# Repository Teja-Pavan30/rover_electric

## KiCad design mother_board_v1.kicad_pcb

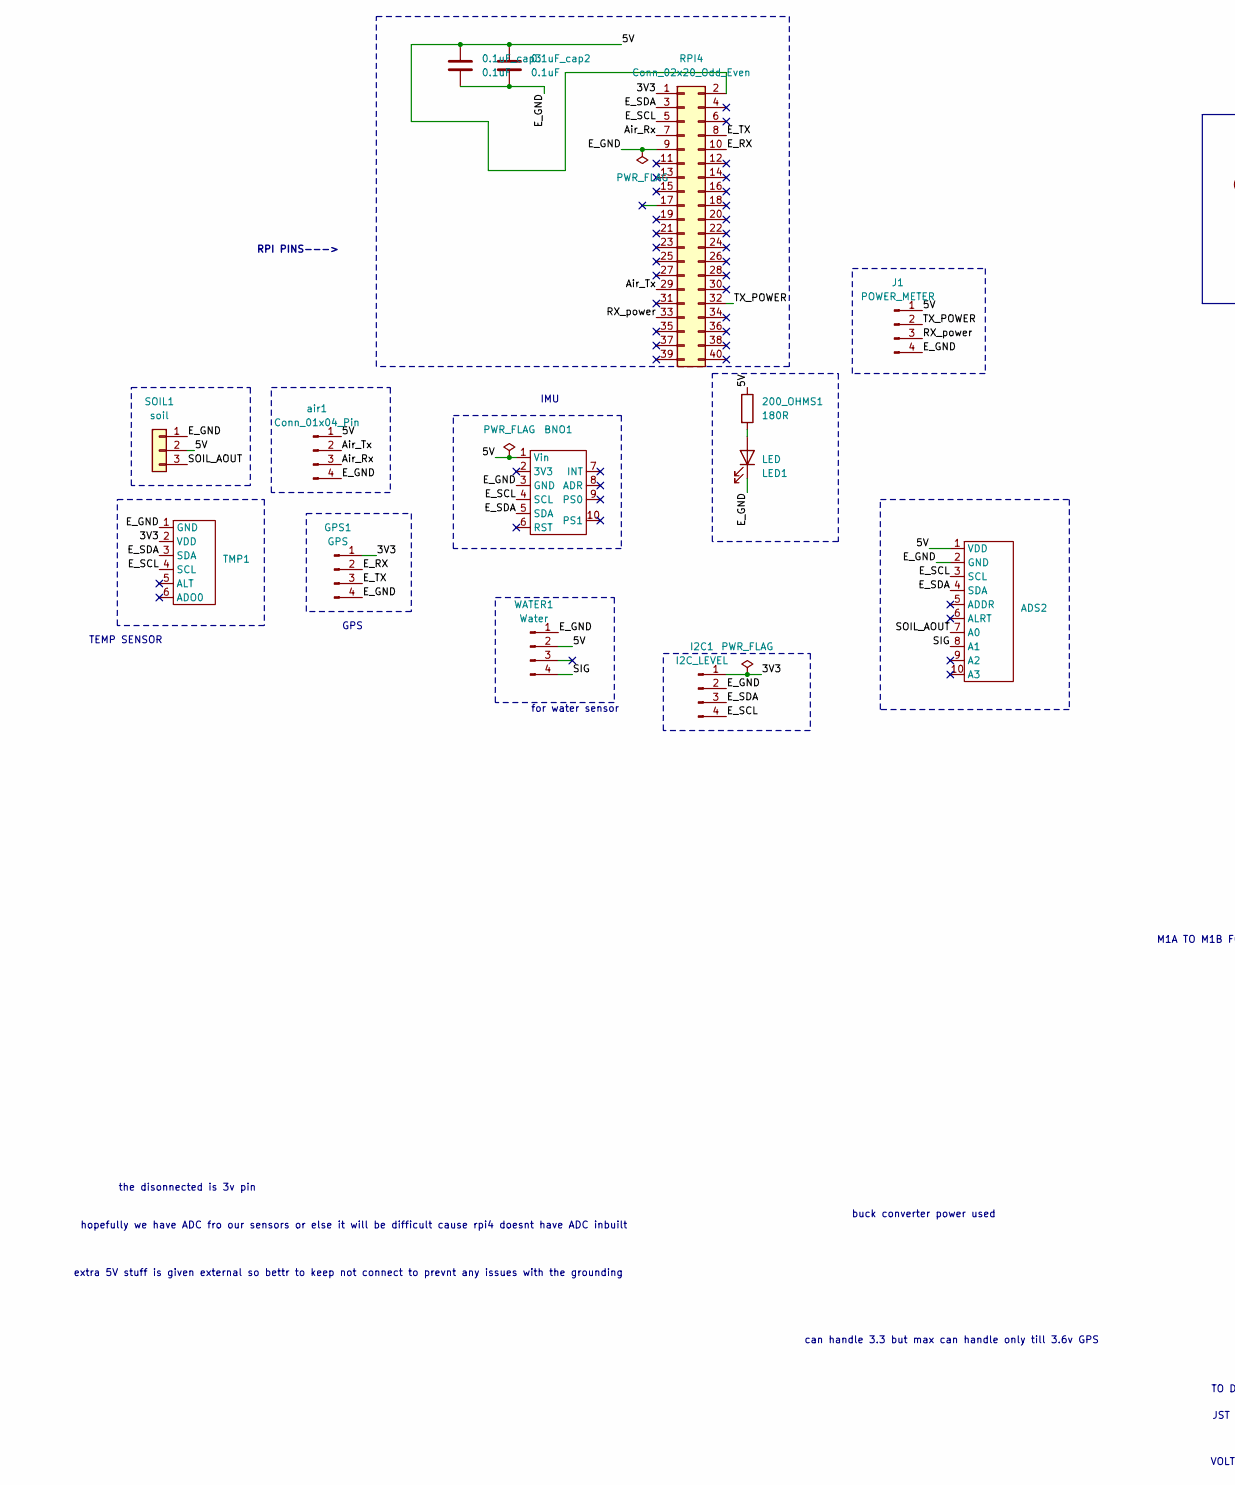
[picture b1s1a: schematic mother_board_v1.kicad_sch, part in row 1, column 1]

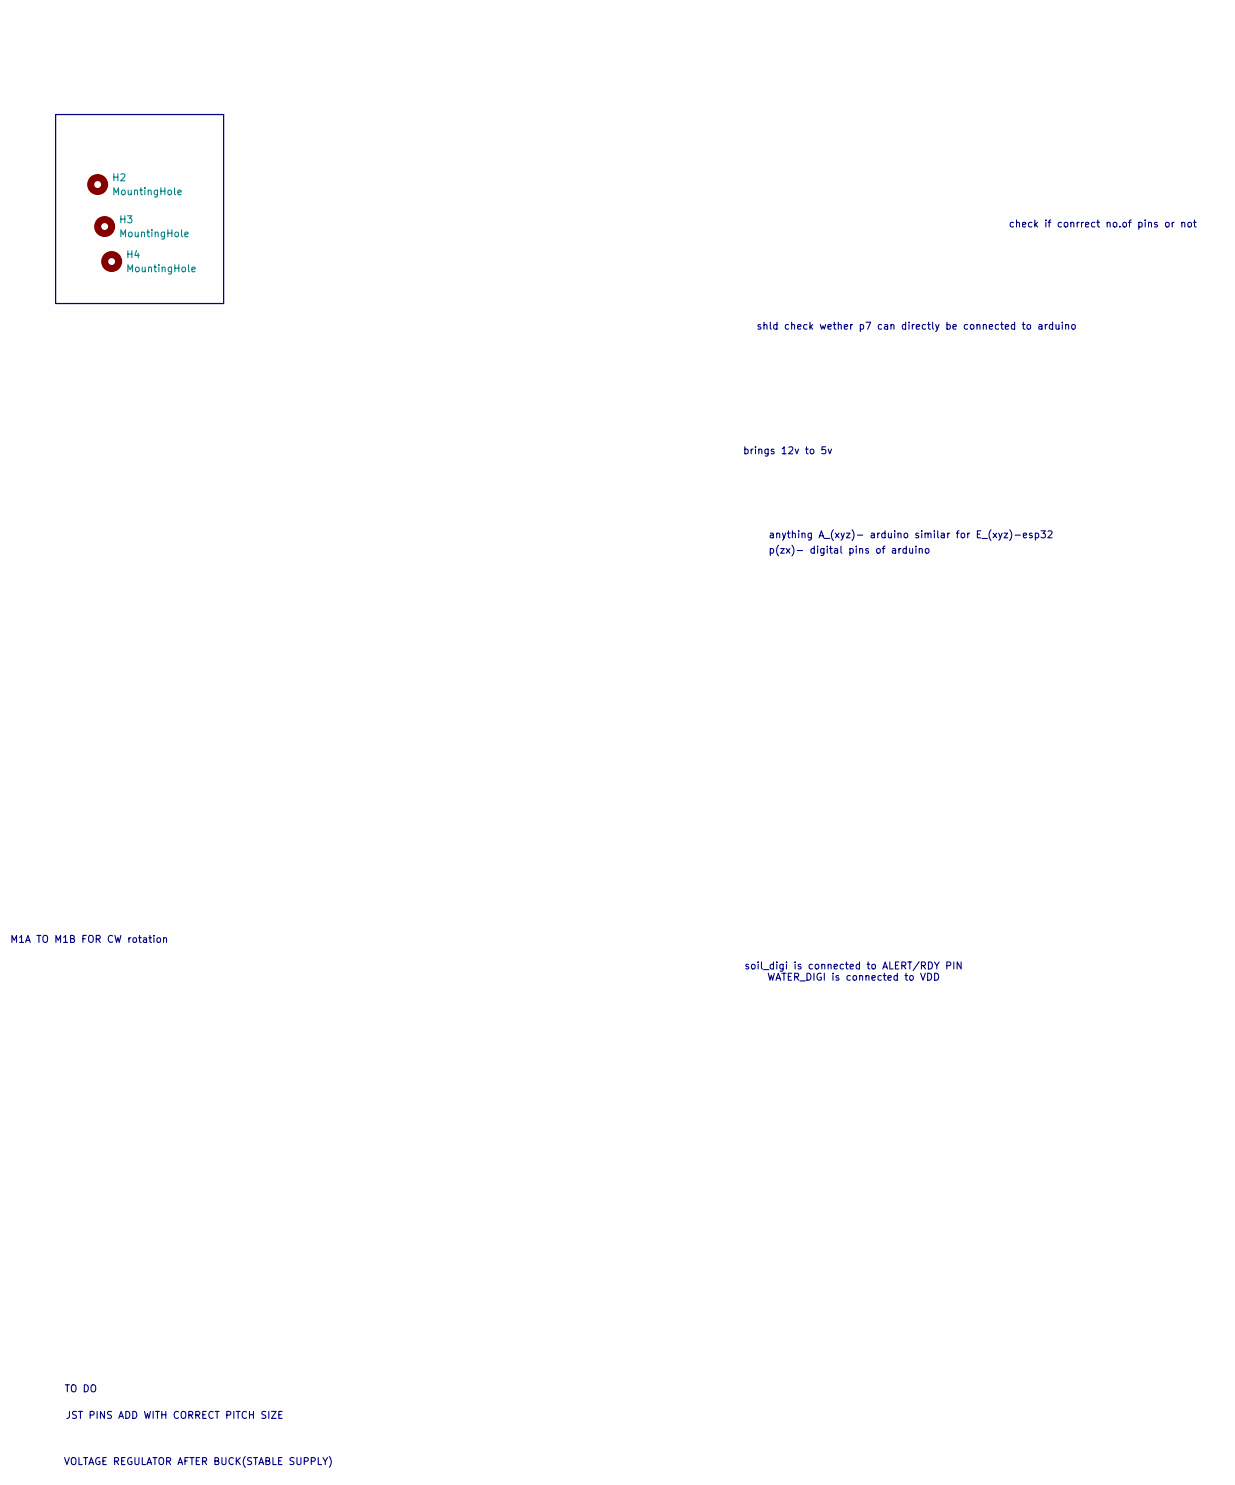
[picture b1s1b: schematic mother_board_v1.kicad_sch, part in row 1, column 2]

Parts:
0.1uF_cap2, 0.1uF_cap3: 0.1uF; C_Disc_D3.0mm_W1.6mm_P2.50mm
200_OHMS1: 180R; R_Axial_DIN0414_L11.9mm_D4.5mm_P15.24mm_Horizontal
ADS2: ADS1115
BNO1: ADAFRUIT-BNO055-STEMMA-QT
GPS1: GPS; JST_XH_B4B-XH-AM_1x04_P2.50mm_Vertical
H2, H3, H4: MountingHole; MountingHole_3.2mm_M3_ISO7380_Pad
I2C1: I2C_LEVEL; JST_XH_B4B-XH-AM_1x04_P2.50mm_Vertical
J1: POWER_METER; JST_XH_B4B-XH-AM_1x04_P2.50mm_Vertical
LED1: LED; LED_D5.0mm
RPI4: Conn_02x20_Odd_Even; IDC-Header_2x20_P2.54mm_Vertical
SOIL1: soil; JST_XH_B3B-XH-A_1x03_P2.50mm_Vertical
TMP1: TMP102
WATER1: Water; JST_XH_B4B-XH-AM_1x04_P2.50mm_Vertical
air1: Conn_01x04_Pin; JST_XH_B4B-XH-AM_1x04_P2.50mm_Vertical

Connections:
/3V3: GPS1.1, I2C1.1, RPI4.1, TMP1.2 (VDD)
/5V: 0.1uF_cap2.2, 0.1uF_cap3.2, 200_OHMS1.1, ADS2.1 (VDD), BNO1.1 (Vin), J1.1, RPI4.2, SOIL1.2, WATER1.2, air1.1
/Air_Rx: RPI4.7, air1.3
/Air_Tx: RPI4.29, air1.2
/E_GND: 0.1uF_cap2.1, 0.1uF_cap3.1, ADS2.2 (GND), BNO1.3 (GND), GPS1.4, I2C1.2, J1.4, LED1.1 (K), RPI4.9, SOIL1.1, TMP1.1 (GND), WATER1.1, air1.4
/E_RX: GPS1.2, RPI4.10
/E_SCL: ADS2.3 (SCL), BNO1.4 (SCL), I2C1.4, RPI4.5, TMP1.4 (SCL)
/E_SDA: ADS2.4 (SDA), BNO1.5 (SDA), I2C1.3, RPI4.3, TMP1.3 (SDA)
/E_TX: GPS1.3, RPI4.8
/RX_power: J1.3, RPI4.33
/SIG: ADS2.8 (A1), WATER1.4
/SOIL_AOUT: ADS2.7 (A0), SOIL1.3
/TX_POWER: J1.2, RPI4.32
unnamed: 200_OHMS1.2, LED1.2 (A)

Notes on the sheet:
anything A_(xyz)- arduino similar for E_(xyz)-esp32
VOLTAGE REGULATOR AFTER BUCK(STABLE SUPPLY)
buck converter power used
extra 5V stuff is given external so bettr to keep not connect to prevnt any issues with the grounding
TEMP SENSOR
M1A TO M1B FOR CW rotation
IMU
for water sensor
brings 12v to 5v
GPS
TO DO
the disonnected is 3v pin
can handle 3.3 but max can handle only till 3.6v GPS
shld check wether p7 can directly be connected to arduino
hopefully we have ADC fro our sensors or else it will be difficult cause rpi4 doesnt have ADC inbuilt
p(zx)- digital pins of arduino
check if conrrect no.of pins or not
soil_digi is connected to ALERT/RDY PIN WATER_DIGI is connected to VDD
RPI PINS--->
JST PINS ADD WITH CORRECT PITCH SIZE

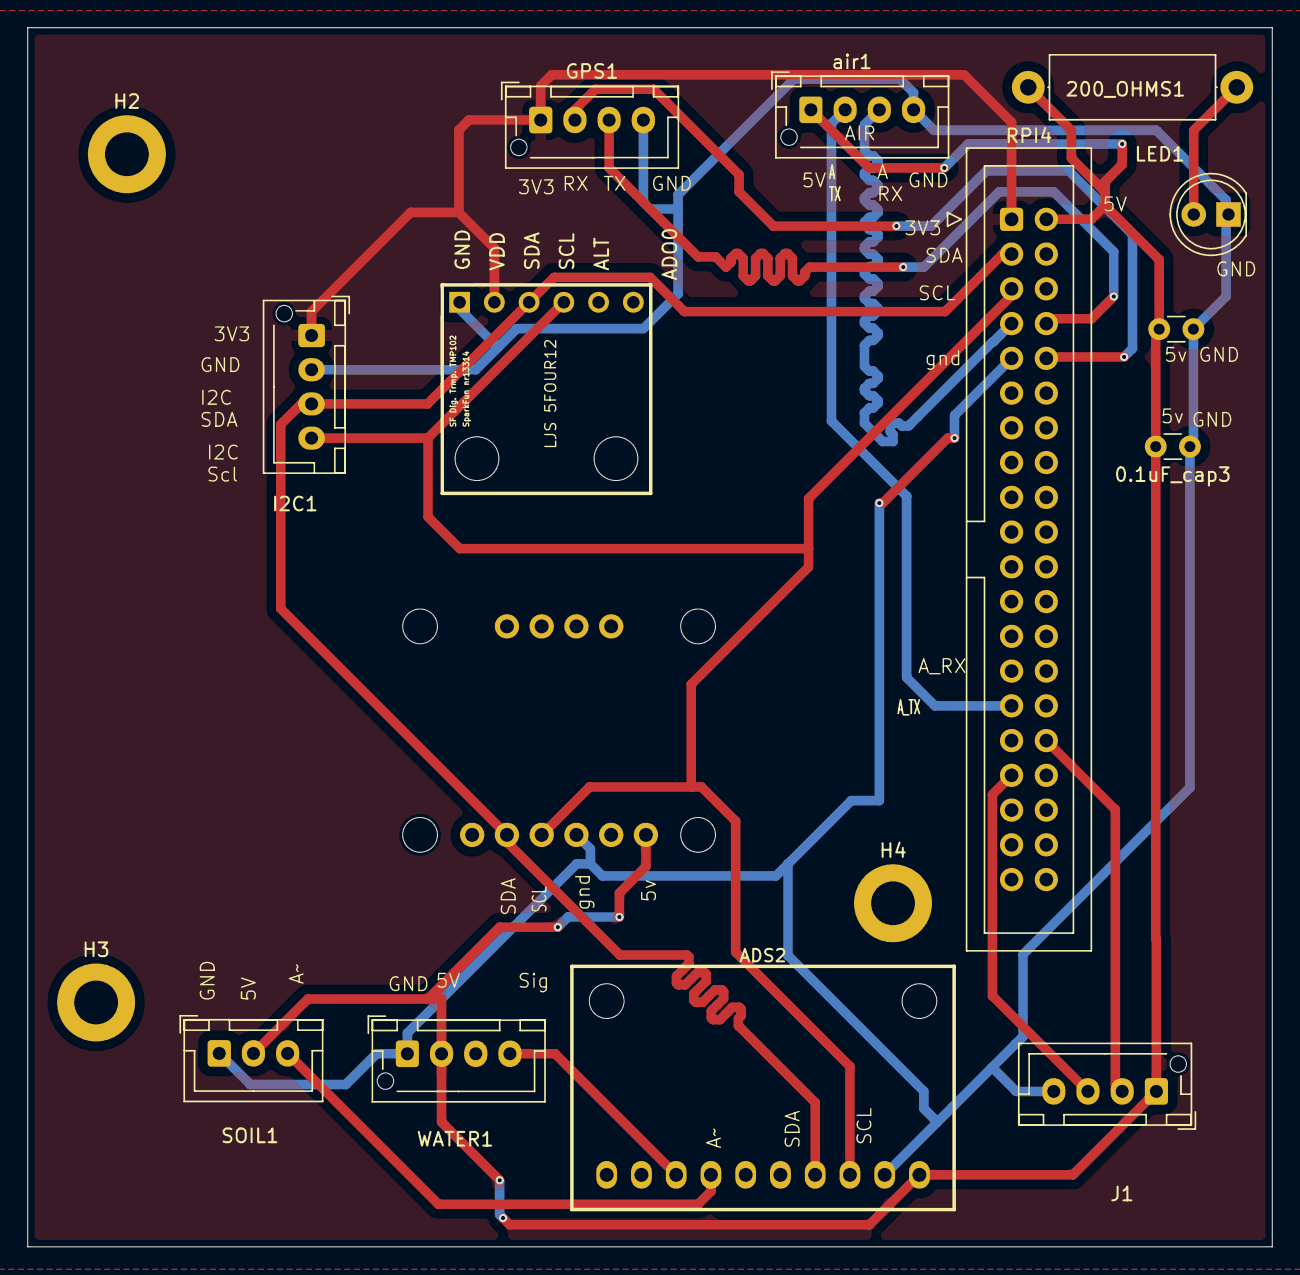
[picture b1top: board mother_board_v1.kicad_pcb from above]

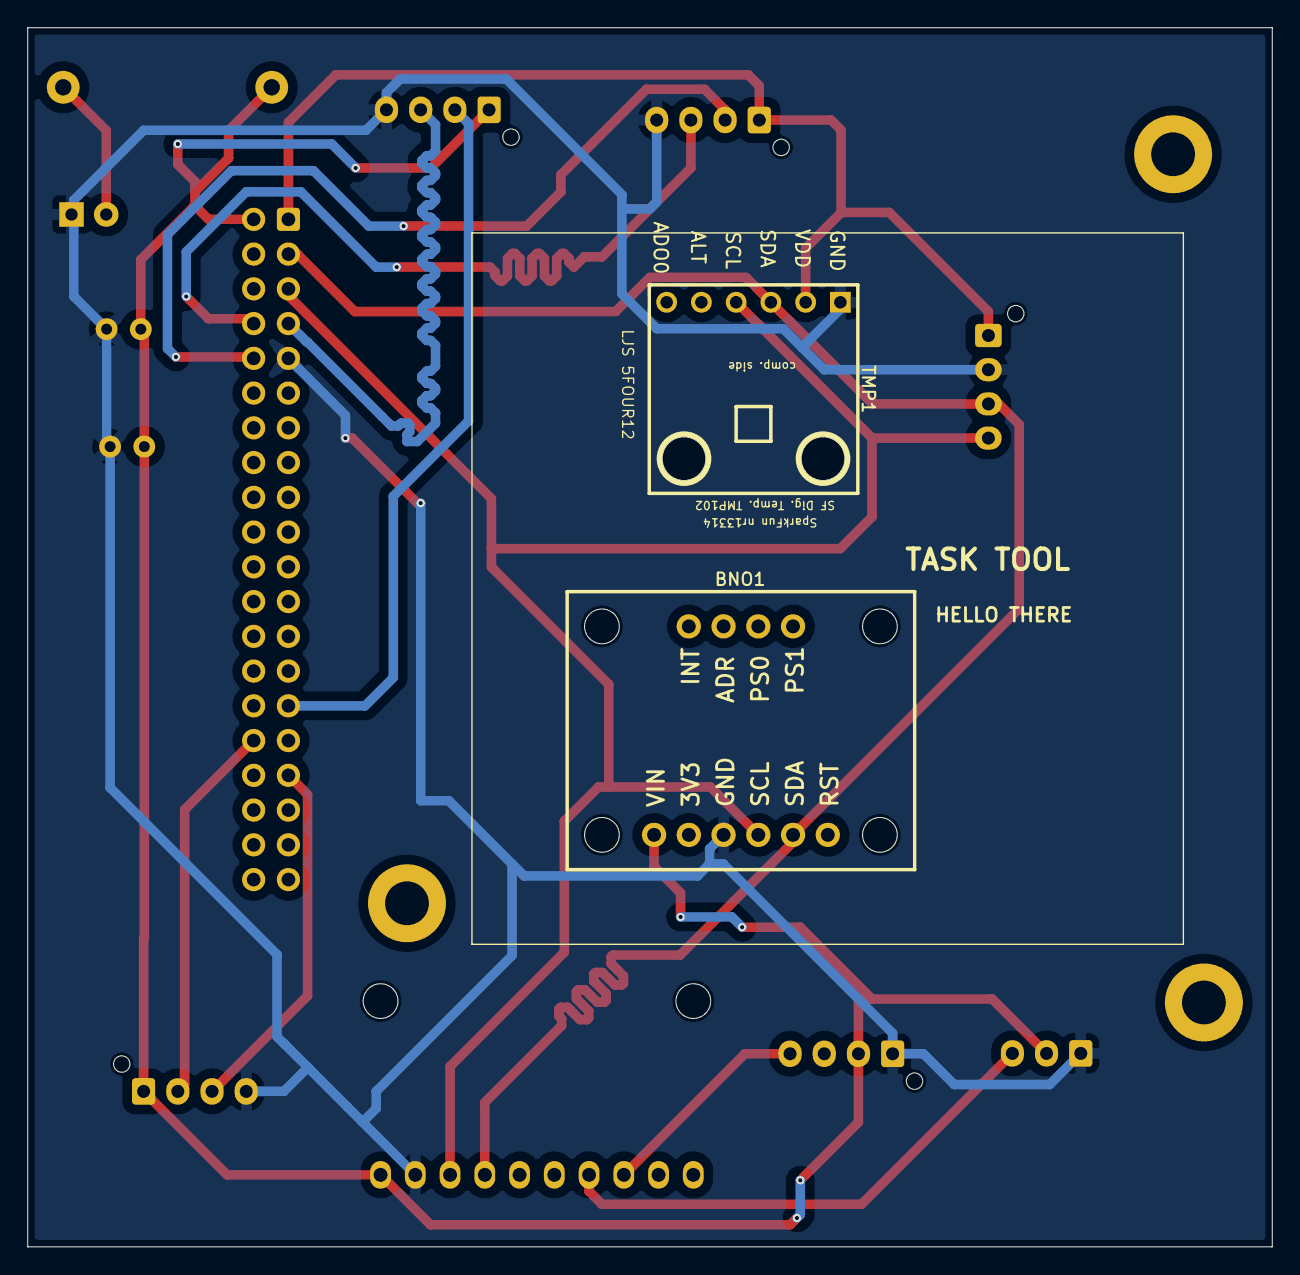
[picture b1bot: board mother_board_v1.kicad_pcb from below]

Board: 2 copper layers, 91.0 x 89.1 mm, 17 parts (2 on the bottom side), 14 nets.

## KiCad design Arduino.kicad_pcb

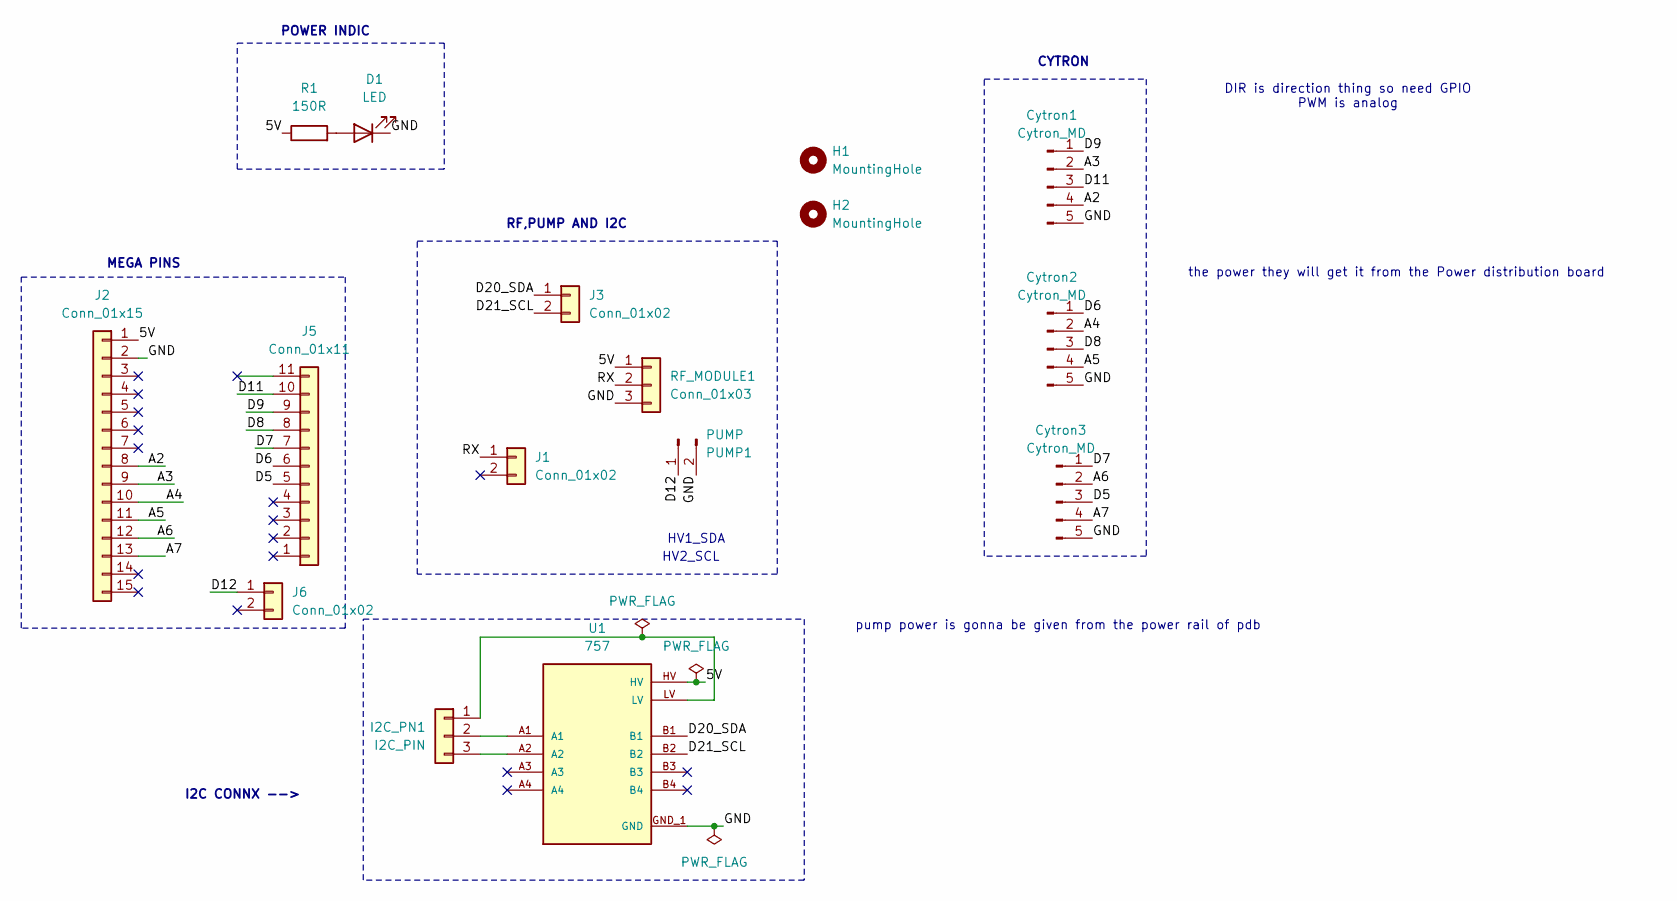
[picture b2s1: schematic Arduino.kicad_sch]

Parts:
Cytron1, Cytron2, Cytron3: Cytron_MD; JST_XH_B5B-XH-A_1x05_P2.50mm_Vertical
D1: LED; LED_D5.0mm
H1, H2: MountingHole; MountingHole_3.2mm_M3_ISO7380
I2C_PN1: I2C_PIN; JST_XH_B3B-XH-AM_1x03_P2.50mm_Vertical
J1, J3, J6: Conn_01x02; PinHeader_1x02_P2.54mm_Vertical
J2: Conn_01x15; PinHeader_1x15_P2.54mm_Vertical
J5: Conn_01x11; PinHeader_1x11_P2.54mm_Vertical
PUMP1: PUMP; JST_XH_B2B-XH-AM_1x02_P2.50mm_Vertical
R1: 150R; R_Axial_DIN0204_L3.6mm_D1.6mm_P5.08mm_Horizontal
RF_MODULE1: Conn_01x03; JST_XH_B3B-XH-A_1x03_P2.50mm_Vertical
U1: 757; MODULE_757; PARTREV N/A

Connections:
/5V: J2.1, R1.1, RF_MODULE1.1, U1.HV
/A2: Cytron1.4, J2.8
/A3: Cytron1.2, J2.9
/A4: Cytron2.2, J2.10
/A5: Cytron2.4, J2.11
/A6: Cytron3.2, J2.12
/A7: Cytron3.4, J2.13
/D5: Cytron3.3, J5.5
/D6: Cytron2.1, J5.6
/D7: Cytron3.1, J5.7
/D8: Cytron2.3, J5.8
/D9: Cytron1.1, J5.9
/D11: Cytron1.3, J5.10
/D12: J6.1, PUMP1.1
/D20_SDA: J3.1, U1.B1
/D21_SCL: J3.2, U1.B2
/RX: J1.1, RF_MODULE1.2
GND: Cytron1.5, Cytron2.5, Cytron3.5, D1.1 (K), J2.2, PUMP1.2, RF_MODULE1.3, U1.GND_1 (GND), U1.GND_2 (GND)
unnamed: D1.2 (A), R1.2
unnamed: I2C_PN1.1, U1.LV
unnamed: I2C_PN1.2, U1.A1
unnamed: I2C_PN1.3, U1.A2

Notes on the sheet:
CYTRON
pump power is gonna be given from the power rail of pdb
DIR is direction thing so need GPIO PWM is analog
the power they will get it from the Power distribution board
I2C CONNX -->
POWER INDIC
RF,PUMP AND I2C
HV2_SCL
MEGA PINS
HV1_SDA

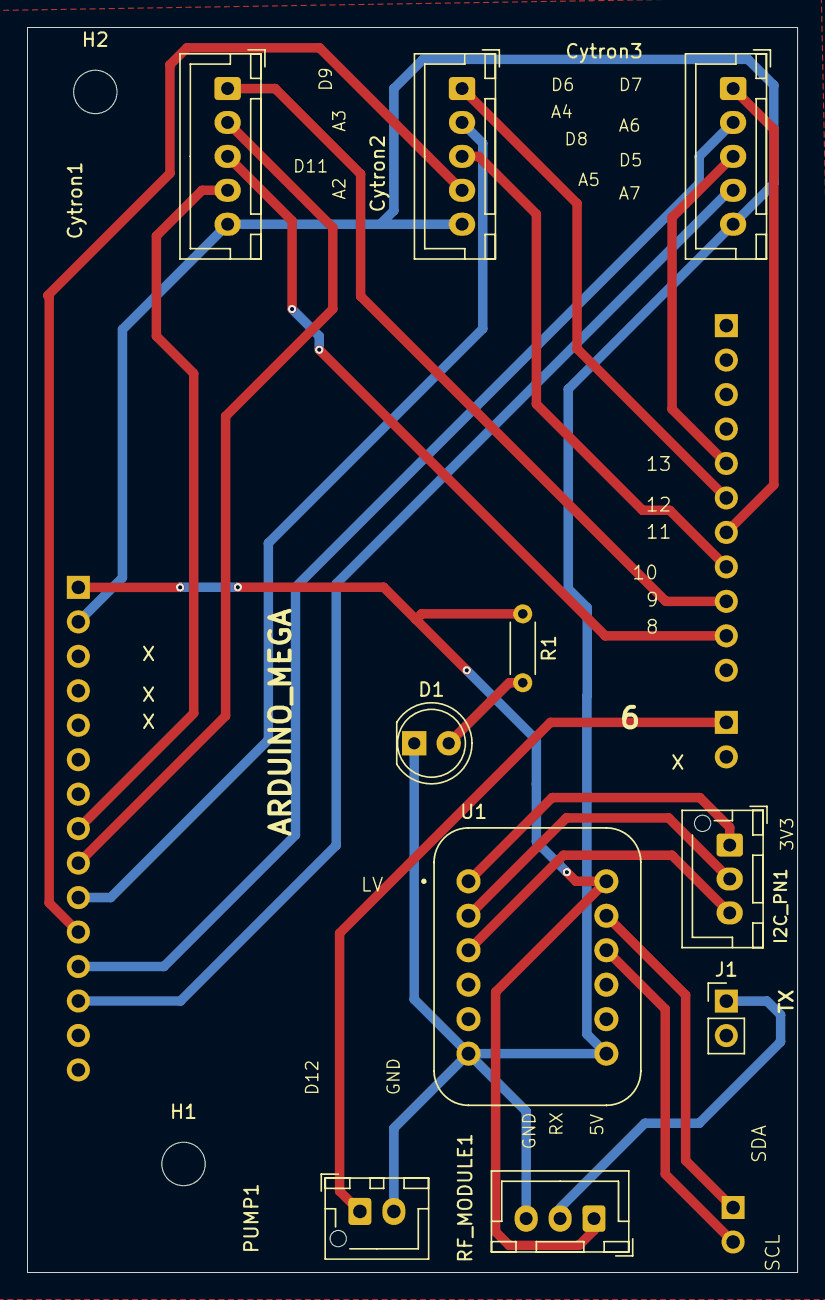
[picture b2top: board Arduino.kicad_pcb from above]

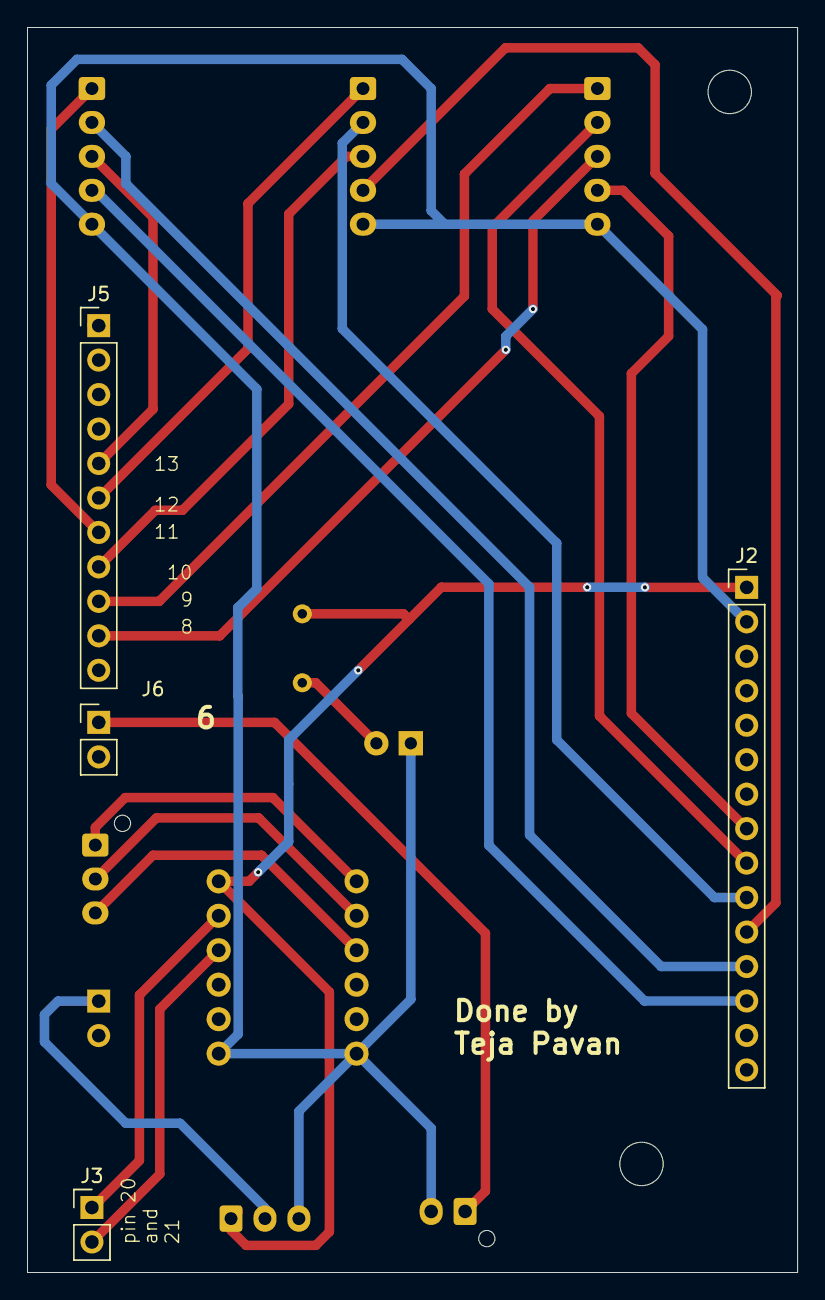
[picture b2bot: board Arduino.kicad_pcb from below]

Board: 2 copper layers, 56.8 x 91.8 mm, 16 parts (4 on the bottom side), 22 nets.
